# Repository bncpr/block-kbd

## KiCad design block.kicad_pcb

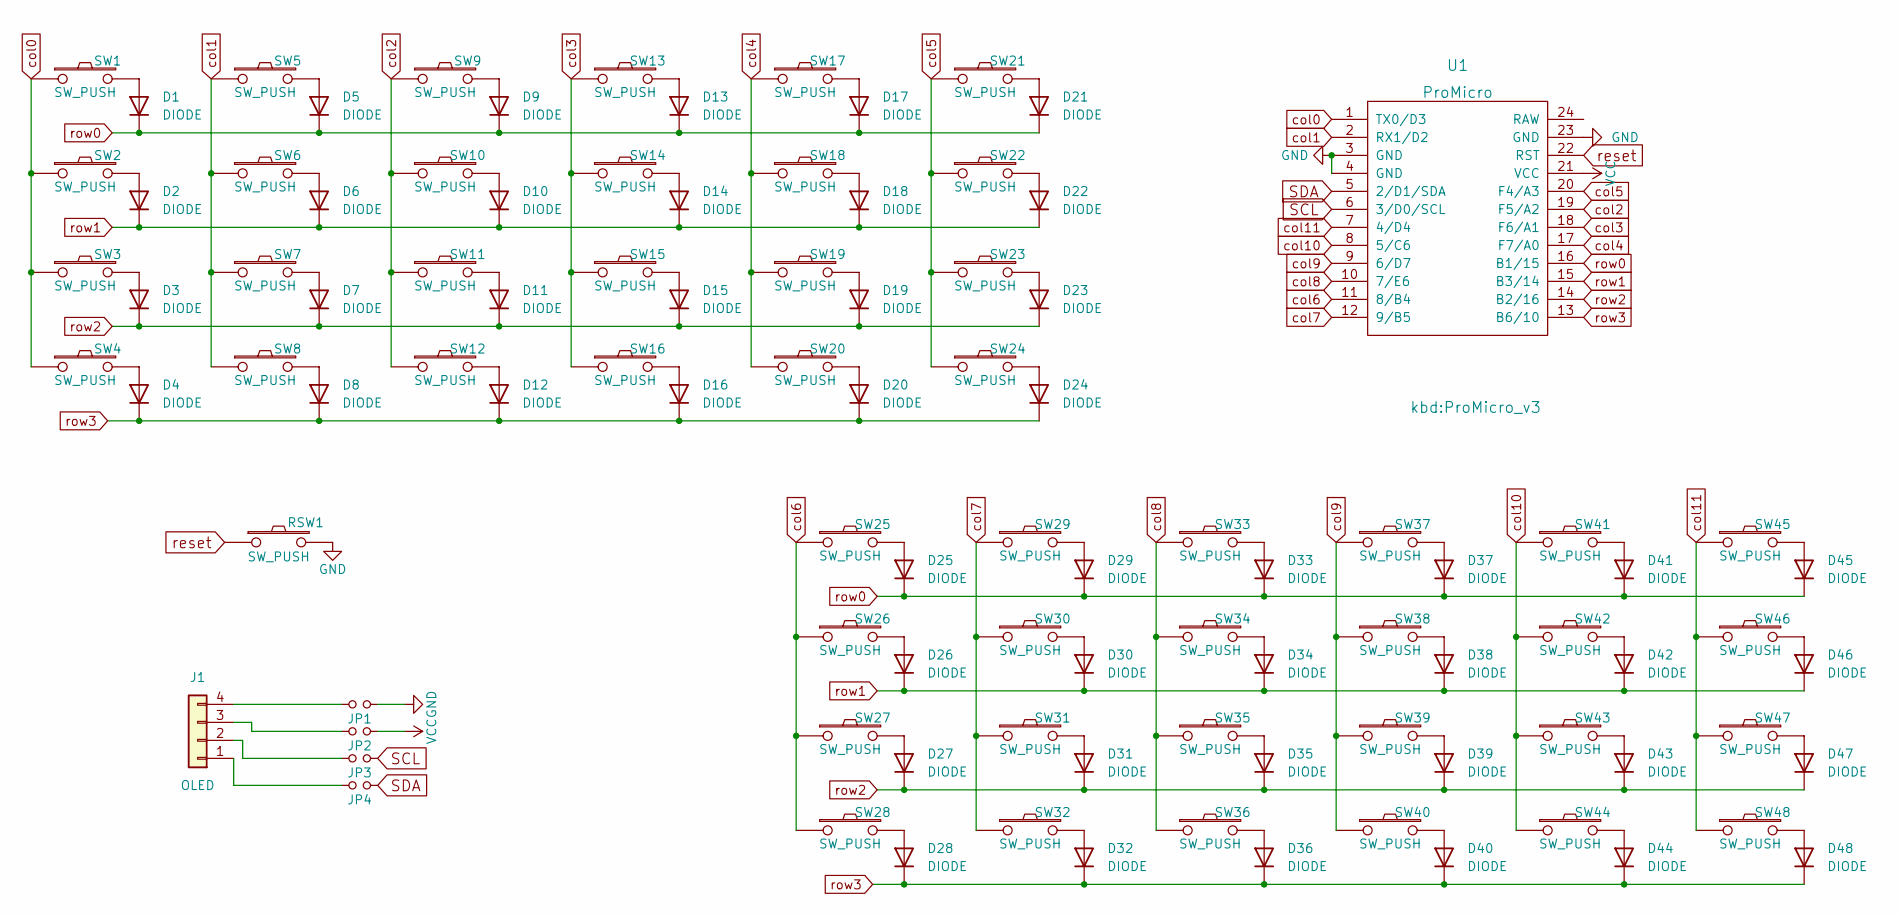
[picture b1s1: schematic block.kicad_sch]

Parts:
D1, D2, D3, D4, D5, D6, D7, D8, D9, D10, D11, D12, D13, D14, D15, D16, D17, D18, D19, D20, D21, D22, D23, D24, D25, D26, D27, D28, D29, D30, D31, D32, D33, D34, D35, D36, D37, D38, D39, D40, D41, D42, D43, D44, D45, D46, D47, D48: DIODE; D3_SMD_v2
J1: OLED
JP1, JP2, JP3, JP4: Jumper
RSW1: SW_PUSH; ResetSW_1side
SW1, SW2, SW3, SW4, SW5, SW6, SW7, SW8, SW9, SW10, SW11, SW12, SW13, SW14, SW15, SW16, SW17, SW18, SW19, SW20, SW21, SW22, SW23, SW24, SW25, SW26, SW27, SW28, SW29, SW30, SW31, SW32, SW33, SW34, SW35, SW36, SW37, SW38, SW39, SW40, SW41, SW42, SW43, SW44, SW45, SW46, SW47, SW48: SW_PUSH; CherryMX_Choc_Hotswap
U1: ProMicro; ProMicro_v3

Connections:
GND: JP1.1, RSW1.2, U1.3 (GND), U1.4 (GND), U1.23 (GND)
unnamed: D1.1 (A), SW1.2
unnamed: D2.1 (A), SW2.2
unnamed: D3.1 (A), SW3.2
unnamed: D4.1 (A), SW4.2
unnamed: D5.1 (A), SW5.2
unnamed: D6.1 (A), SW6.2
unnamed: D7.1 (A), SW7.2
unnamed: D8.1 (A), SW8.2
unnamed: D9.1 (A), SW9.2
unnamed: D10.1 (A), SW10.2
unnamed: D11.1 (A), SW11.2
unnamed: D12.1 (A), SW12.2
unnamed: D13.1 (A), SW13.2
unnamed: D14.1 (A), SW14.2
unnamed: D15.1 (A), SW15.2
unnamed: D16.1 (A), SW16.2
unnamed: D17.1 (A), SW17.2
unnamed: D18.1 (A), SW18.2
unnamed: D19.1 (A), SW19.2
unnamed: D20.1 (A), SW20.2
unnamed: D21.1 (A), SW21.2
unnamed: D22.1 (A), SW22.2
unnamed: D23.1 (A), SW23.2
unnamed: D24.1 (A), SW24.2
unnamed: D25.1 (A), SW25.2
unnamed: D26.1 (A), SW26.2
unnamed: D27.1 (A), SW27.2
unnamed: D28.1 (A), SW28.2
unnamed: D29.1 (A), SW29.2
unnamed: D30.1 (A), SW30.2
unnamed: D31.1 (A), SW31.2
unnamed: D32.1 (A), SW32.2
unnamed: D33.1 (A), SW33.2
unnamed: D34.1 (A), SW34.2
unnamed: D35.1 (A), SW35.2
unnamed: D36.1 (A), SW36.2
unnamed: D37.1 (A), SW37.2
unnamed: D38.1 (A), SW38.2
unnamed: D39.1 (A), SW39.2
unnamed: D40.1 (A), SW40.2
unnamed: D41.1 (A), SW41.2
unnamed: D42.1 (A), SW42.2
unnamed: D43.1 (A), SW43.2
unnamed: D44.1 (A), SW44.2
unnamed: D45.1 (A), SW45.2
unnamed: D46.1 (A), SW46.2
unnamed: D47.1 (A), SW47.2
unnamed: D48.1 (A), SW48.2
unnamed: J1.1, JP4.2
unnamed: J1.2, JP3.2
unnamed: J1.3, JP2.2
unnamed: J1.4, JP1.2
SCL: JP3.1, U1.6 (3/D0/SCL)
SDA: JP4.1, U1.5 (2/D1/SDA)
VCC: JP2.1, U1.21 (VCC)
col0: SW1.1, SW2.1, SW3.1, SW4.1, U1.1 (TX0/D3)
col1: SW5.1, SW6.1, SW7.1, SW8.1, U1.2 (RX1/D2)
col2: SW9.1, SW10.1, SW11.1, SW12.1, U1.19 (F5/A2)
col3: SW13.1, SW14.1, SW15.1, SW16.1, U1.18 (F6/A1)
col4: SW17.1, SW18.1, SW19.1, SW20.1, U1.17 (F7/A0)
col5: SW21.1, SW22.1, SW23.1, SW24.1, U1.20 (F4/A3)
col6: SW25.1, SW26.1, SW27.1, SW28.1, U1.11 (8/B4)
col7: SW29.1, SW30.1, SW31.1, SW32.1, U1.12 (9/B5)
col8: SW33.1, SW34.1, SW35.1, SW36.1, U1.10 (7/E6)
col9: SW37.1, SW38.1, SW39.1, SW40.1, U1.9 (6/D7)
col10: SW41.1, SW42.1, SW43.1, SW44.1, U1.8 (5/C6)
col11: SW45.1, SW46.1, SW47.1, SW48.1, U1.7 (4/D4)
reset: RSW1.1, U1.22 (RST)
row0: D1.2 (K), D5.2 (K), D9.2 (K), D13.2 (K), D17.2 (K), D21.2 (K), D25.2 (K), D29.2 (K), D33.2 (K), D37.2 (K), D41.2 (K), D45.2 (K), U1.16 (B1/15)
row1: D2.2 (K), D6.2 (K), D10.2 (K), D14.2 (K), D18.2 (K), D22.2 (K), D26.2 (K), D30.2 (K), D34.2 (K), D38.2 (K), D42.2 (K), D46.2 (K), U1.15 (B3/14)
row2: D3.2 (K), D7.2 (K), D11.2 (K), D15.2 (K), D19.2 (K), D23.2 (K), D27.2 (K), D31.2 (K), D35.2 (K), D39.2 (K), D43.2 (K), D47.2 (K), U1.14 (B2/16)
row3: D4.2 (K), D8.2 (K), D12.2 (K), D16.2 (K), D20.2 (K), D24.2 (K), D28.2 (K), D32.2 (K), D36.2 (K), D40.2 (K), D44.2 (K), D48.2 (K), U1.13 (B6/10)

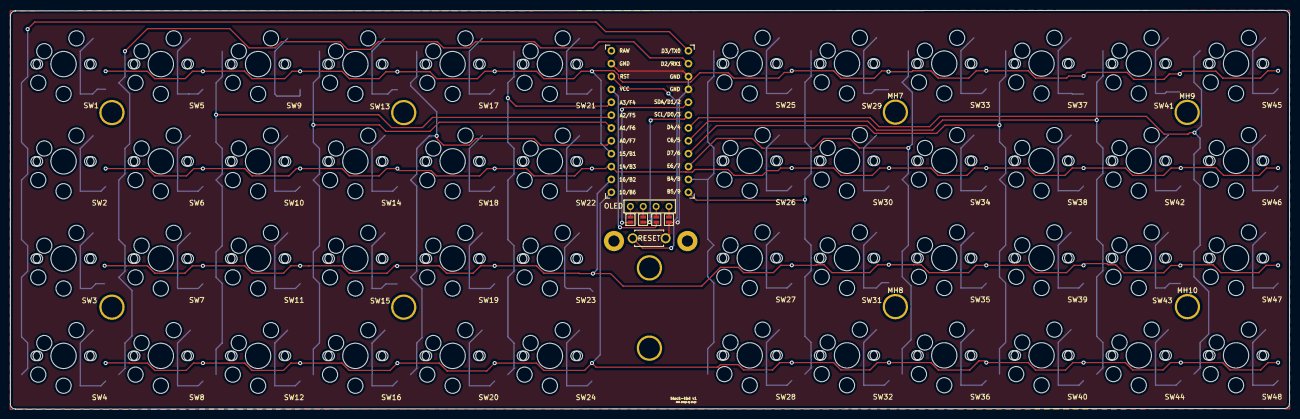
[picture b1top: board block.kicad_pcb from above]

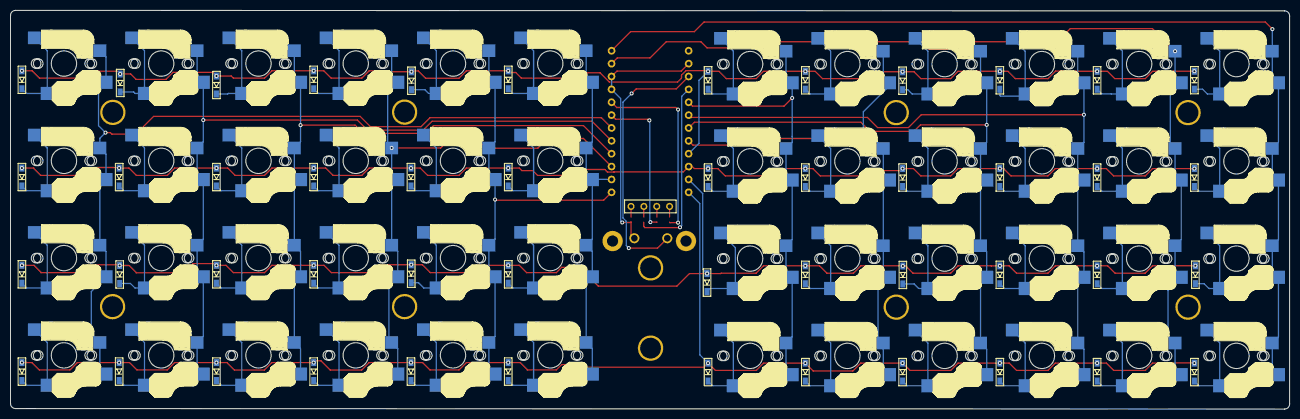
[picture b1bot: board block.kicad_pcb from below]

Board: 2 copper layers, 252.5 x 78.7 mm, 113 parts (48 on the bottom side), 73 nets.

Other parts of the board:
MH1, MH2, MH3, MH4, MH5, MH6, MH7, MH8, MH9, MH10: M2; LEGO_HOLE

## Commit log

2022-12-29 init
2022-12-29 block board
2022-12-30 add ground fills
2022-12-30 mounting holes
2022-12-30 add plates
2023-01-21 plates submodule
